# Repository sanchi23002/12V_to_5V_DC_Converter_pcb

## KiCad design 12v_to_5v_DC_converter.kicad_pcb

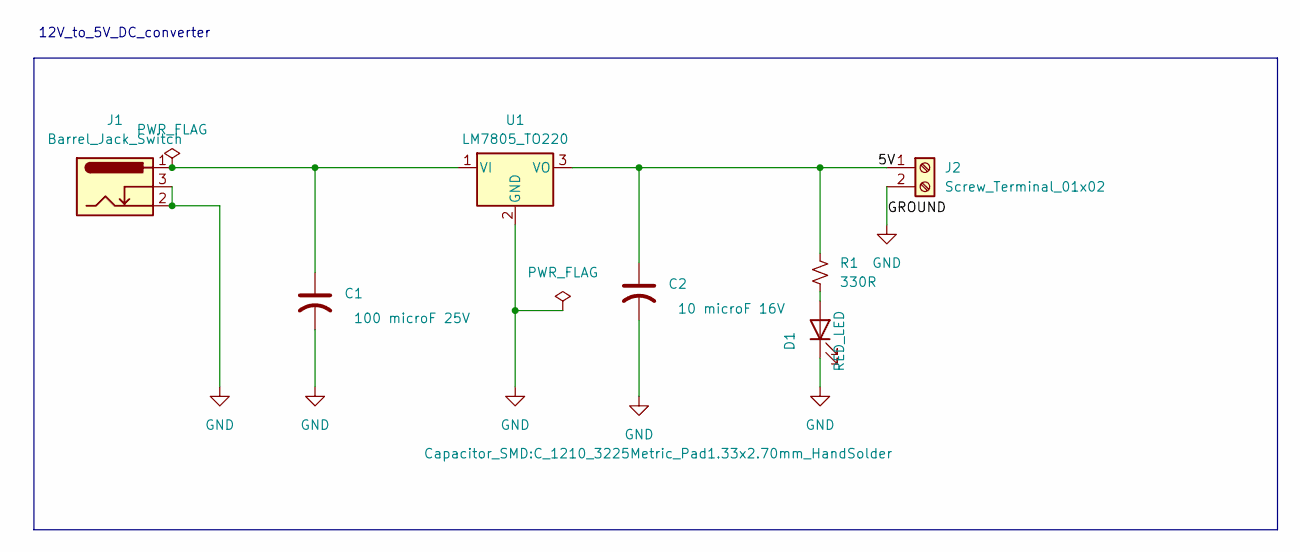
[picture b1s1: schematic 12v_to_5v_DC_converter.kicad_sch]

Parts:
C1: 100 microF 25V; CP_Elec_8x6.2
C2: 10 microF 16V; C_1210_3225Metric_Pad1.33x2.70mm_HandSolder
D1: RED_LED; LED_0805_2012Metric
J1: Barrel_Jack_Switch; BarrelJack_CUI_PJ-102AH_Horizontal
J2: Screw_Terminal_01x02; TerminalBlock_MaiXu_MX126-5.0-02P_1x02_P5.00mm
R1: 330R; R_0402_1005Metric_Pad0.72x0.64mm_HandSolder
U1: LM7805_TO220; TO-220-3_Vertical

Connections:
/5V: C2.1, J2.1, R1.1, U1.3 (VO)
GND: C1.2, C2.2, D1.1 (K), J1.2, J1.3, J2.2, U1.2 (GND)
unnamed: D1.2 (A), R1.2
unnamed: C1.1, J1.1, U1.1 (VI)

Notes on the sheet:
12V_to_5V_DC_converter

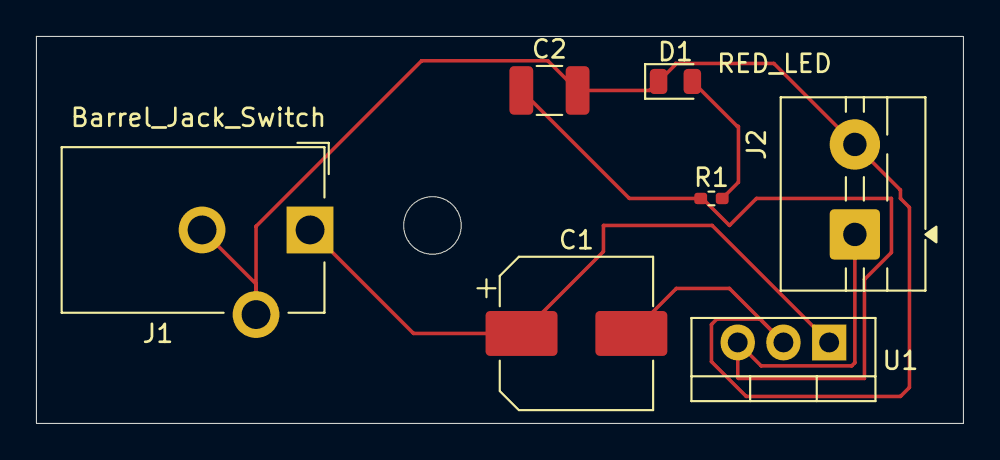
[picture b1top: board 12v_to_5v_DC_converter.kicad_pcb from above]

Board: 2 copper layers, 51.5 x 21.5 mm, 7 parts (0 on the bottom side), 4 nets.
